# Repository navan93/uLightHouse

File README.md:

# firefly
A tiny LED circuit which lights up in the dark.

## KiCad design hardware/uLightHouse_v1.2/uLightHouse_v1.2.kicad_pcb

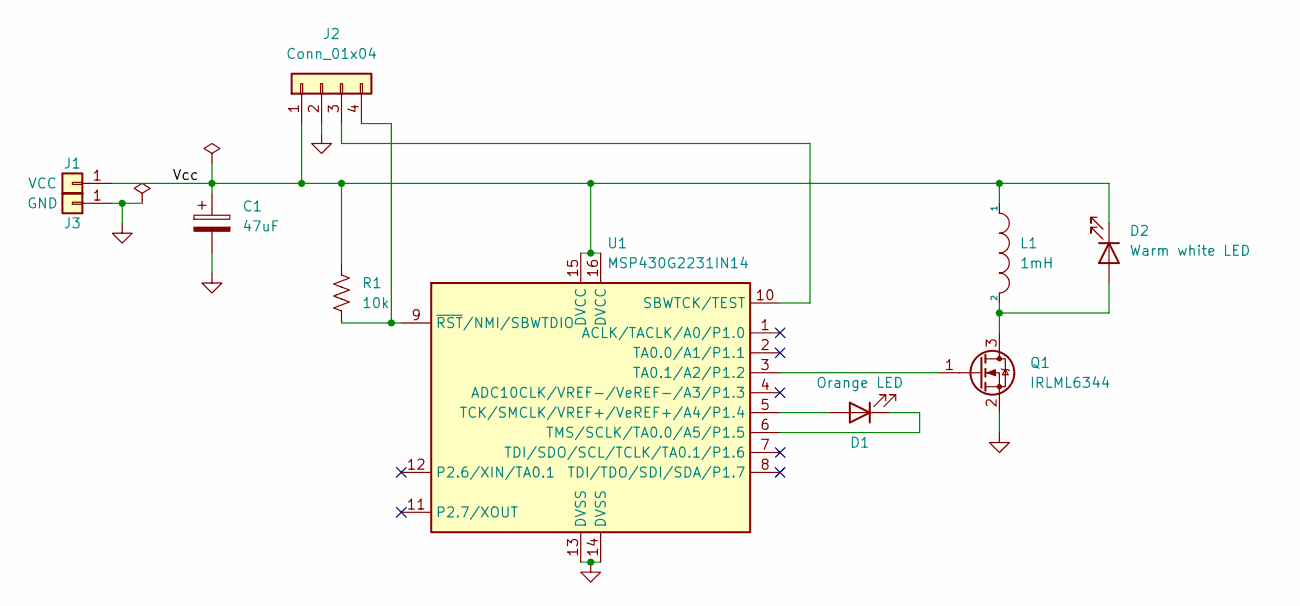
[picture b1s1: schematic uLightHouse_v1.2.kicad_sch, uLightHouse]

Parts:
C1: 47uF; C_1210_3225Metric_Pad1.33x2.70mm_HandSolder
D1: Orange LED; LED_0805_2012Metric_Pad1.15x1.40mm_HandSolder
D2: Warm white LED; TestPoint_2Pads_Pitch2.54mm_Drill0.8mm
J1: VCC; TestPoint_Pad_D1.5mm
J2: Conn_01x04; PinHeader_1x04_P1.27mm_Vertical
J3: GND; TestPoint_Pad_D1.5mm
L1: 1mH; L_TTElectronics_HM79M-20xxx
Q1: IRLML6344; SOT-23
R1: 10k; R_0603_1608Metric_Pad0.98x0.95mm_HandSolder
U1: MSP430G2231IN14; Texas_S-PVQFN-N16_EP2.7x2.7mm

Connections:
/Vcc: C1.1, D2.1 (K), J1.1, J2.1, L1.1, R1.1, U1.15 (DVCC), U1.16 (DVCC)
GND: C1.2, J2.2, J3.1, Q1.2 (S), U1.13 (DVSS), U1.14 (DVSS)
unnamed: D1.2 (A), U1.5 (TCK/SMCLK/VREF+/VeREF+/A4/P1.4)
unnamed: D1.1 (K), U1.6 (TMS/SCLK/TA0.0/A5/P1.5)
unnamed: D2.2 (A), L1.2, Q1.3 (D)
unnamed: J2.3, U1.10 (SBWTCK/TEST)
unnamed: J2.4, R1.2, U1.9 (~RST/NMI/SBWTDIO)
unnamed: Q1.1 (G), U1.3 (TA0.1/A2/P1.2)

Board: 2 copper layers, 10 parts (4 on the bottom side), 8 nets, no tracks yet.

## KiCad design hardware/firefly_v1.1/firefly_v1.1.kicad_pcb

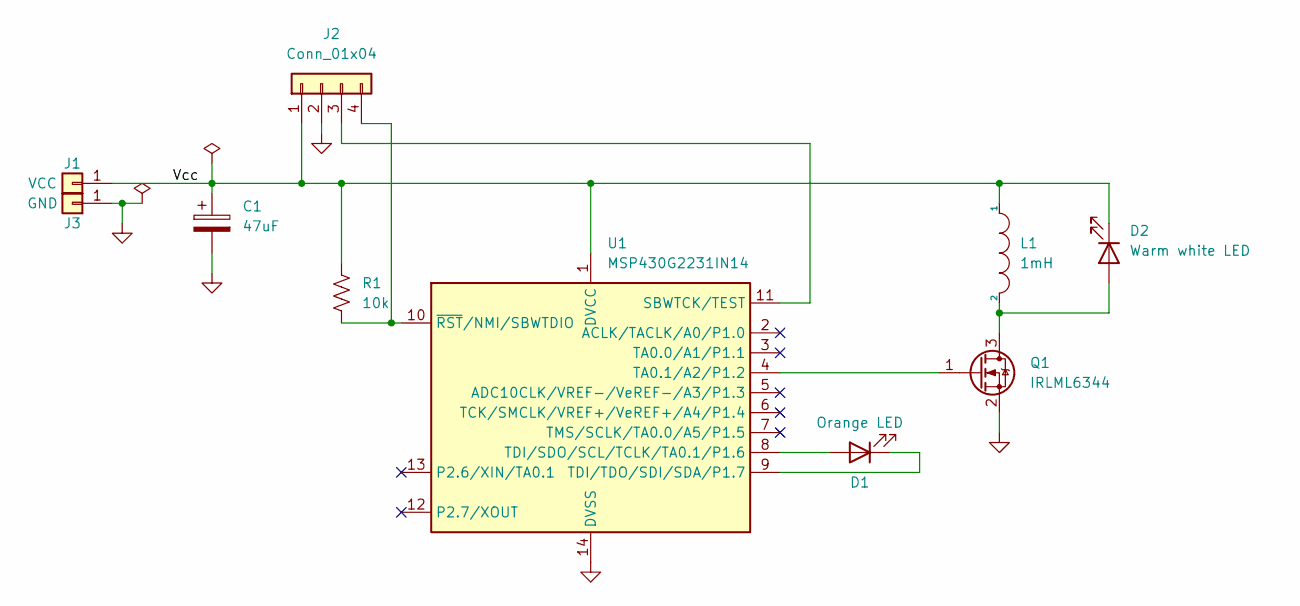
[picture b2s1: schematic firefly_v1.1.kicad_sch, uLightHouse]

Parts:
C1: 47uF; C_1210_3225Metric_Pad1.33x2.70mm_HandSolder
D1: Orange LED; LED_0805_2012Metric_Pad1.15x1.40mm_HandSolder
D2: Warm white LED; TestPoint_2Pads_Pitch2.54mm_Drill0.8mm
J1: VCC; TestPoint_Pad_D1.5mm
J2: Conn_01x04; PinHeader_1x04_P2.54mm_Vertical
J3: GND; TestPoint_Pad_D1.5mm
L1: 1mH; HM79M20102LFTR
Q1: IRLML6344; SOT-23
R1: 10k; R_0603_1608Metric_Pad0.98x0.95mm_HandSolder
U1: MSP430G2231IN14; DIP-14_W7.62mm

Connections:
/Vcc: C1.1, D2.1 (K), J1.1, J2.1, L1.1, R1.1, U1.1 (DVCC)
GND: C1.2, J2.2, J3.1, Q1.2 (S), U1.14 (DVSS)
unnamed: D1.2 (A), U1.8 (TDI/SDO/SCL/TCLK/TA0.1/P1.6)
unnamed: D1.1 (K), U1.9 (TDI/TDO/SDI/SDA/P1.7)
unnamed: D2.2 (A), L1.2, Q1.3 (D)
unnamed: J2.3, U1.11 (SBWTCK/TEST)
unnamed: J2.4, R1.2, U1.10 (~RST/NMI/SBWTDIO)
unnamed: Q1.1 (G), U1.4 (TA0.1/A2/P1.2)

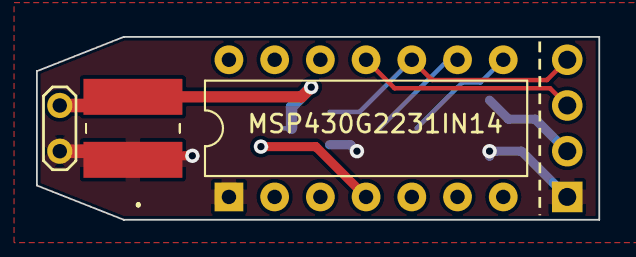
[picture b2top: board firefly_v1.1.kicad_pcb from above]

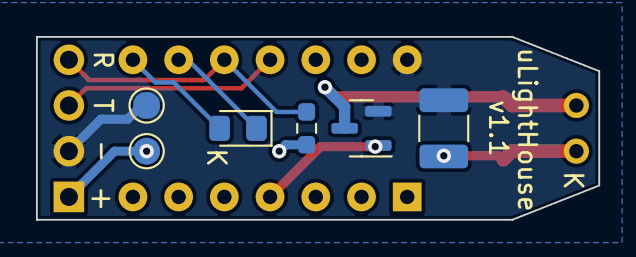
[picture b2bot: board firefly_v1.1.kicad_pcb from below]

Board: 2 copper layers, 31.2 x 10.2 mm, 10 parts (6 on the bottom side), 8 nets.

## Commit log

2023-06-06 Create directory structure
    Add initial CSS project
2023-06-06 Simple LPM3 test code
    which blinks an LED.
2023-06-06 Initial schematic
2023-06-27 First basic functional code
2023-07-01 Beacon mode tests
2023-07-01 Beacon mode 2 tests
2023-07-02 Add darkness detection and enhance brightness
2023-07-03 hardware rev1 commit
2023-09-16 Bump KiCad to version 7
2023-09-16 Create v1.1 from v1 clone
2023-09-17 Initial placement done
2023-09-17 Completed routing
2023-09-18 Cleanup DRC warnings and errors, released for fab
2023-09-19 Switch to footprint from curated global libs
2023-09-20 Match the changes in repo name
2023-09-20 Match changes in project name
2023-09-23 Initial placement for a smaller form factor,
    add datasheet and user guide for easy reference
2023-10-21 v1.1 HW Pilot run
    Cleanup unused functions, rename the project to match hardware,
    add a simple adaptive darkness threshold.
2023-10-21 Add docs
